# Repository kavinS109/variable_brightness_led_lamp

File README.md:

# Variable Brightness LED Lamp

A custom LED lamp designed from schematic through PCB, firmware,
mechanical enclosure, and final assembly.

## Requirements

- The lamp shall provide a control mechanism that allows the user to turn the light on and off, and adjust its brightness.
- The lamp shall operate from a 5V DC input supplied from an AC-to-DC wall adapter.
- The lamp shall incorporate a custom PCB designed to fit within and mount to a 3D-printed enclosure.

## System Architecture

## 3D CAD Model

[View the lamp in 3D](hardware/cad/lamp_v1.stl)

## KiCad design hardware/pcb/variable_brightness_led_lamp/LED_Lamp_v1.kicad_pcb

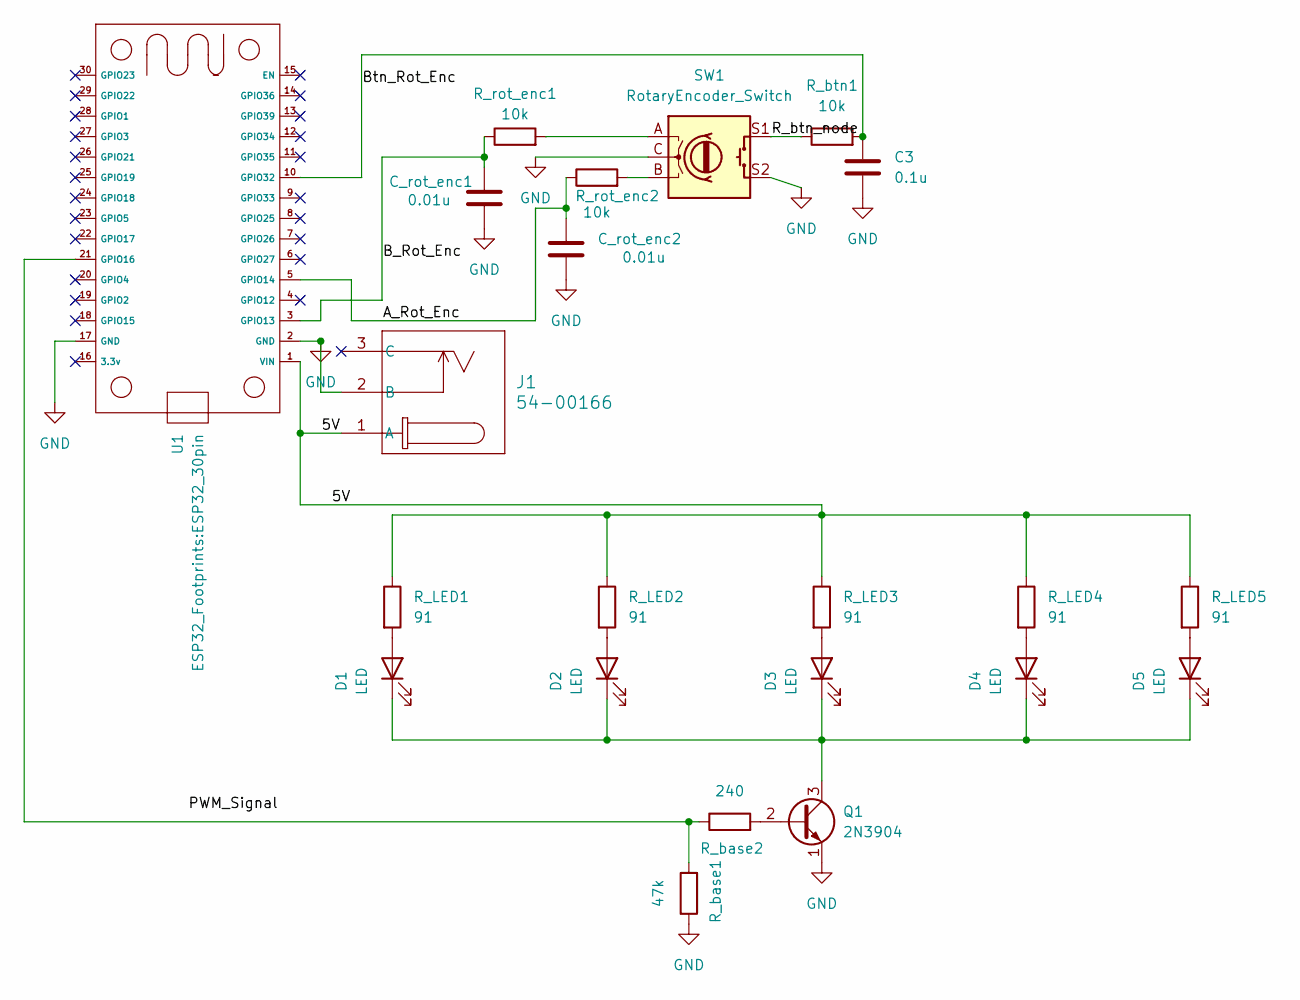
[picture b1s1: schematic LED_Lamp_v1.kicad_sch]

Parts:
C3: 0.1u; C_Disc_D5.0mm_W2.5mm_P2.50mm
C_rot_enc1, C_rot_enc2: 0.01u; C_Disc_D5.0mm_W2.5mm_P2.50mm
D1, D2, D3, D4, D5: LED; LED_D5.0mm
J1: 54-00166; CONN3_54-00166_TEN
Q1: 2N3904; TO-92_Inline
R_LED1, R_LED2, R_LED3, R_LED4, R_LED5: 91; R_Axial_DIN0207_L6.3mm_D2.5mm_P7.62mm_Horizontal
R_base1: 47k; R_Axial_DIN0207_L6.3mm_D2.5mm_P7.62mm_Horizontal
R_base2: 240; R_Axial_DIN0207_L6.3mm_D2.5mm_P7.62mm_Horizontal
R_btn1: 10k; R_Axial_DIN0207_L6.3mm_D2.5mm_P7.62mm_Horizontal
R_rot_enc1, R_rot_enc2: 10k; R_Axial_DIN0207_L6.3mm_D2.5mm_P7.62mm_Horizontal
SW1: RotaryEncoder_Switch; RotaryEncoder_Alps_EC11E-Switch_Vertical_H20mm_CircularMoun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
U1: ESP32_30pin

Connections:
/5V: J1.1 (A), R_LED1.1, R_LED2.1, R_LED3.1, R_LED4.1, R_LED5.1, U1.1 (VIN)
/A_Rot_Enc: C_rot_enc2.1, R_rot_enc2.1, U1.5 (GPIO14)
/B_Rot_Enc: C_rot_enc1.1, R_rot_enc1.1, U1.3 (GPIO13)
/Btn_Rot_Enc: C3.1, R_btn1.2, U1.10 (GPIO32)
/R_btn_node: R_btn1.1, SW1.S1
GND: C3.2, C_rot_enc1.2, C_rot_enc2.2, J1.2 (B), Q1.1 (E), R_base1.1, SW1.C, SW1.S2, U1.2 (GND), U1.17 (GND)
unnamed: D1.2 (A), R_LED1.2
unnamed: D1.1 (K), D2.1 (K), D3.1 (K), D4.1 (K), D5.1 (K), Q1.3 (C)
unnamed: D2.2 (A), R_LED2.2
unnamed: D3.2 (A), R_LED3.2
unnamed: D4.2 (A), R_LED4.2
unnamed: D5.2 (A), R_LED5.2
unnamed: Q1.2 (B), R_base2.2
unnamed: R_rot_enc1.2, SW1.A
unnamed: R_rot_enc2.2, SW1.B
unnamed: R_base1.2, R_base2.1, U1.21 (GPIO16)

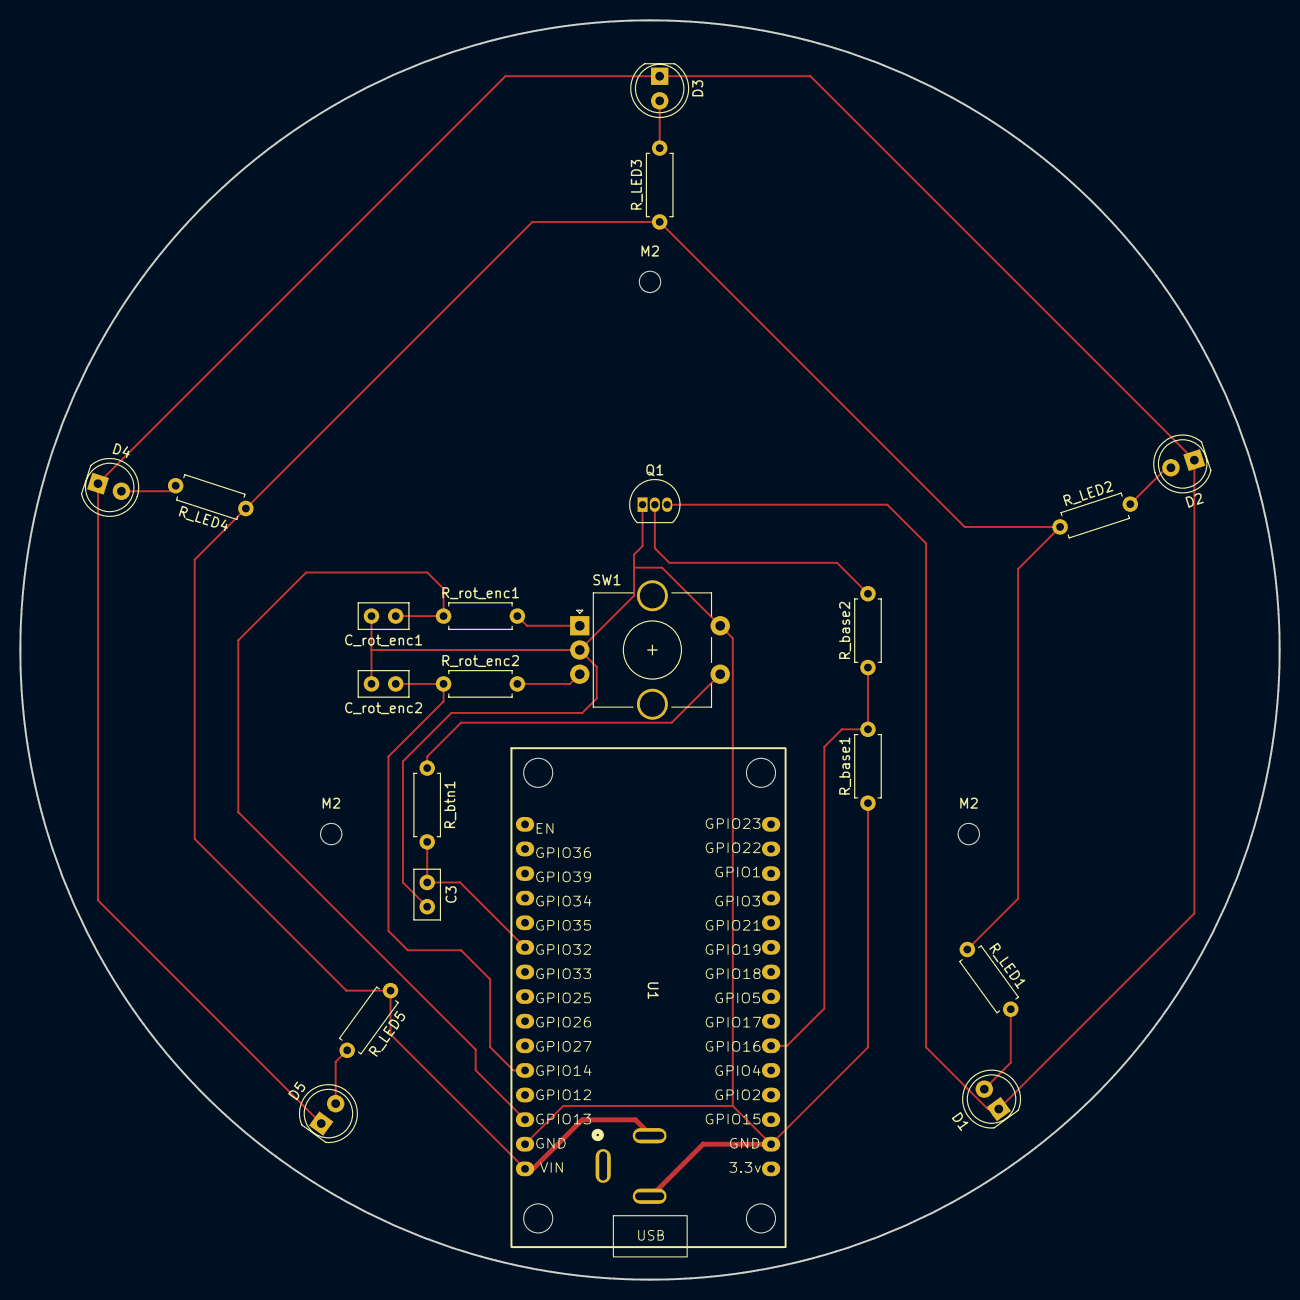
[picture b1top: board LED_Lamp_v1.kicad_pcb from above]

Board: 2 copper layers, 130.0 x 130.0 mm, 25 parts (1 on the bottom side), 16 nets.

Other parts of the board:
M2, M2#2, M2#3: MountingHole_2.2mm_M2
